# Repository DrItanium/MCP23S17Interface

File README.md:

A simple PCB to make using the MCP23S17 DIP-28 very trivial.

I use these ICs in place of 595s and 165s in a bidirectional design.

Revision 3 will be the oldest visible as I did not gitify until that point.

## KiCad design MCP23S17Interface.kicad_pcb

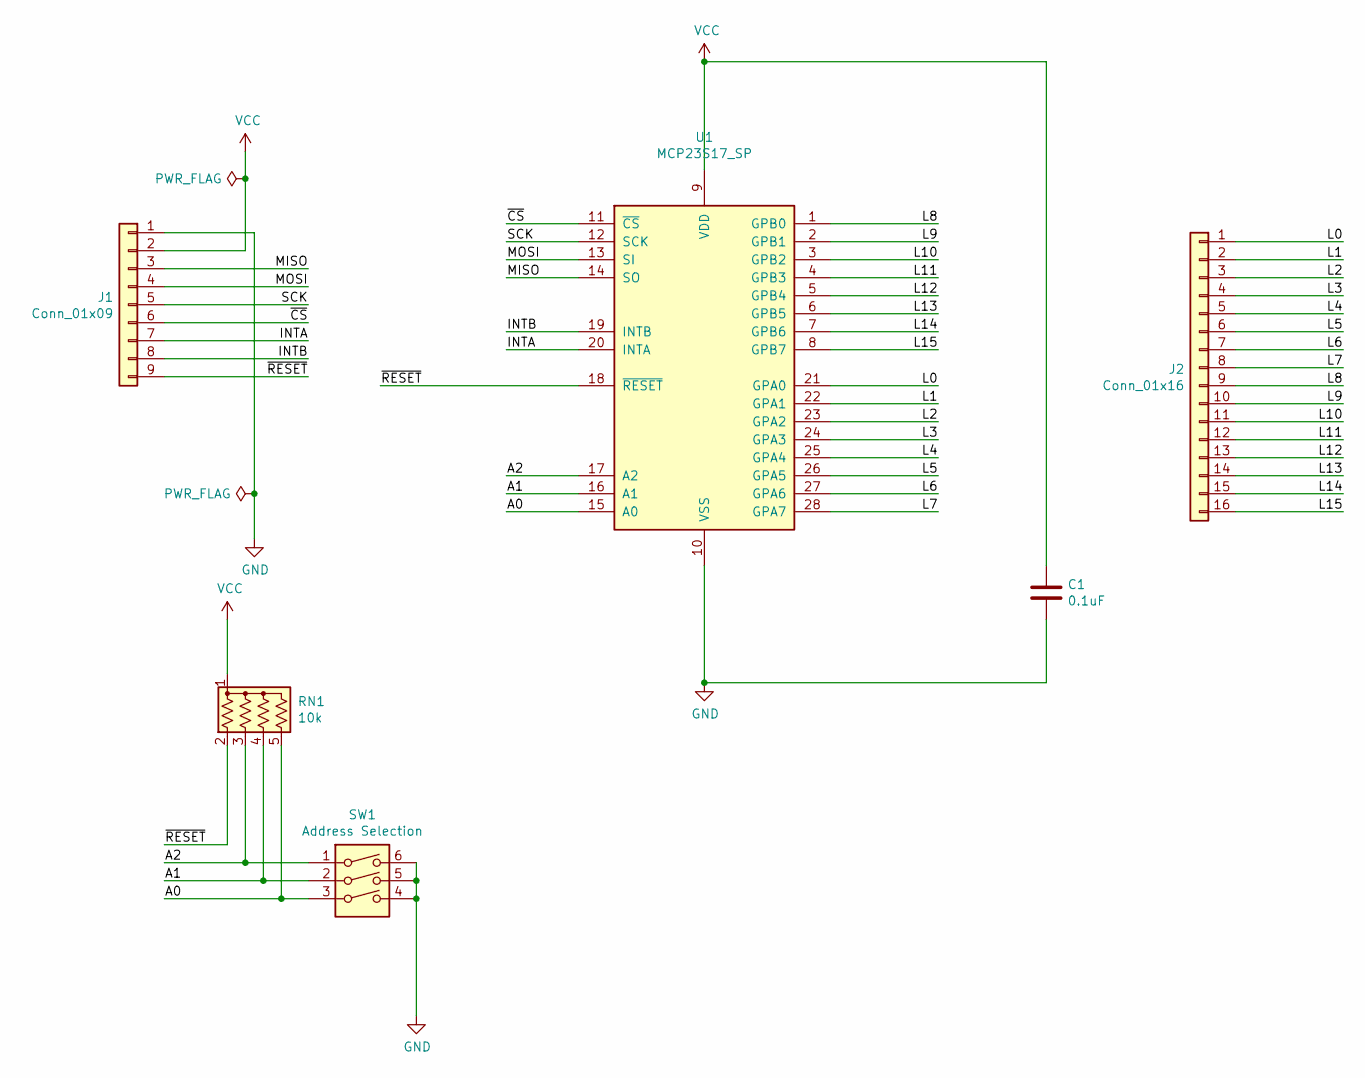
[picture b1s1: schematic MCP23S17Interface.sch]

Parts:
C1: 0.1uF; C_0805_HandSoldering
J1: Conn_01x09; PinHeader_1x09_P2.54mm_Vertical
J2: Conn_01x16; PinHeader_1x16_P2.54mm_Vertical
RN1: 10k; R_Array_SIP5
SW1: Address Selection; DIPSWITCH-03
U1: MCP23S17_SP; DIP-28_W7.62mm

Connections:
/A0: RN1.5 (R4), SW1.3, U1.15 (A0)
/A1: RN1.4 (R3), SW1.2, U1.16 (A1)
/A2: RN1.3 (R2), SW1.1, U1.17 (A2)
/INTA: J1.7, U1.20 (INTA)
/INTB: J1.8, U1.19 (INTB)
/L0: J2.1, U1.21 (GPA0)
/L1: J2.2, U1.22 (GPA1)
/L2: J2.3, U1.23 (GPA2)
/L3: J2.4, U1.24 (GPA3)
/L4: J2.5, U1.25 (GPA4)
/L5: J2.6, U1.26 (GPA5)
/L6: J2.7, U1.27 (GPA6)
/L7: J2.8, U1.28 (GPA7)
/L8: J2.9, U1.1 (GPB0)
/L9: J2.10, U1.2 (GPB1)
/L10: J2.11, U1.3 (GPB2)
/L11: J2.12, U1.4 (GPB3)
/L12: J2.13, U1.5 (GPB4)
/L13: J2.14, U1.6 (GPB5)
/L14: J2.15, U1.7 (GPB6)
/L15: J2.16, U1.8 (GPB7)
/MISO: J1.3, U1.14 (SO)
/MOSI: J1.4, U1.13 (SI)
/SCK: J1.5, U1.12 (SCK)
/~CS: J1.6, U1.11 (~CS~)
/~RESET: J1.9, RN1.2 (R1), U1.18 (~RESET~)
GND: C1.2, J1.1, SW1.4, SW1.5, SW1.6, U1.10 (VSS)
VCC: C1.1, J1.2, RN1.1 (common), U1.9 (VDD)

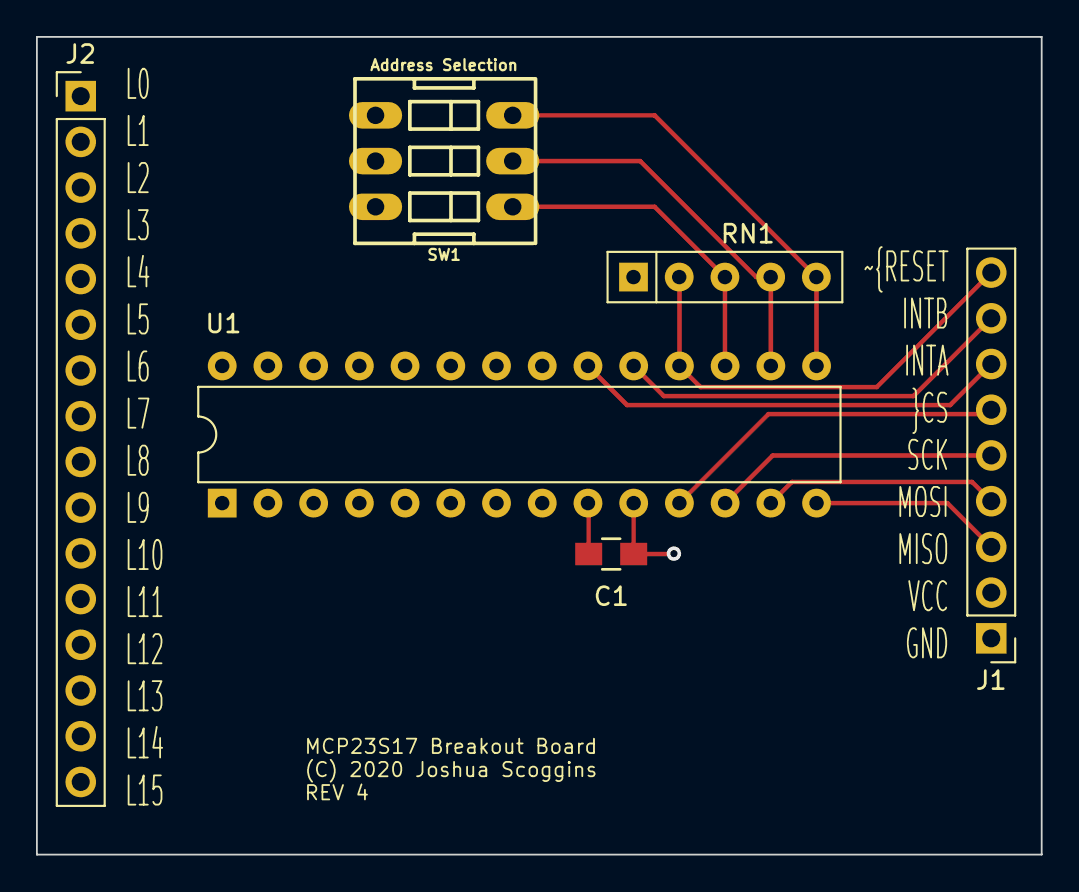
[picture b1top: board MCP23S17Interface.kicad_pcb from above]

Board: 2 copper layers, 55.8 x 45.4 mm, 6 parts (0 on the bottom side), 28 nets.

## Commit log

2020-11-19 Added a readme
2020-11-19 REV 3 hardware
2020-11-19 Start working on rev4
2020-11-19 Replace the jumpered address selection with a dip switch box
    Also, a 10k x 4 pull up resistor network in place of several 805 10k
    resistors.
2020-11-19 Start working on the new PCB
    Rearrange ordering of dip switches to make routing easier
2020-11-19 Finished the rev 4 design
    I have routed the resistor network directly into the trace but I'm not
    sure if that is the smarter design or not. I will ponder further on this
2020-11-19 Rearrange lines further to reduce trace fanout
2020-11-19 Moved the connector up

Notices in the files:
MCP23S17Interface.kicad_pcb:
(C) 2020 Joshua Scoggins
